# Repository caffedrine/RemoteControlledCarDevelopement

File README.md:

## RC Car Developement

Designing and implementing a remote controlled rover from zero to hero!

## Summary:
  1. Project information: [RC_Car_WordDoc.odt](docs/RC_Car_Developement.odt)
  2. Required list of components: [here](Components.md)
  3. How to build: [here](How-to-build.md)
  4. Firmware upload and debugging: [here](Firmware-upload.md)
  
*Costs:* ~60EUR

## Results

## Connections 

#### 1. Connection indicator LED
This is a LED whose meant is to indicate whether there is a connection established with car or not.
It have three states:
  1. Turned off - this mean that a connection is established with car and no further incoming connections will be accepted;
  2. Blinking - No clients connected to car AP nor Sockets are oppened;
  3. Blinking faster - Clients connected to AP but no sockets oppened. If use Java developed app, possibly application is not running.

#### 2. Traffic indicator LED
This is a LED whose meant is to act like any regular ethernet traffic indicator. Whether there is a data exchange between client and car this led will blink. Efficient feedback to confirm if your data is being received by car and vice-versa.

#### 3. Left QRE1113 IR Sensor
Connector for left wheel sensor.

#### 4. RESET Button
This is a push button which will reset car. Whether connection is not responding or you're unable to connect, presh this button and program will reset.

#### 5. Motors connector
Connect motors to this socket using the given pairs. First two entries for left motor and last two entries for right motor. In case motors are reversed, just switch polarity to get the correct rotation direction. 
PS: Do not cross connections between motors!!!

#### 6. IO0
This is a push button and is used to turn microcontroller into programming mode. Whether you want to upload a new firmware, you'll have to use this button in the following way:
Push IO0 and keep it pushed >> once RESET button (don't keep it pushed) >> release IO button. Now the microcontrolled will enter on programing mode and a new firmware can be uploaded using ping pins from point 7.

#### 7. Programming connectors
This is the socket used to upload a new firmware on mictrocontroller. Pins are active only when microcontroller is turned on on programming mode using point 6 (above).
Usually you coonnect pins to a Serial-2-USB converter.
**WARNING:** Logical levels are 0-3.3V. Applying 5V may broke the board.

#### 8. Right QRE1113 IR Sensor
Connector for right wheel sensor.

**Notes:**
  * future versions have a power switch on right-bottom edge;
  * micro USB connection is in bottom layer right beside motors connector;

## How to control the car
Turn the power on by connecting cable to powerbank and swith on. After few seconds, connection led should blink indicating that car is waiting for a incomming conenction. To control the car, two connection phases are required:
1. Connecting to AP - This is the exactly like connecting to any regular router or hotspot. This is possible because car will automatically will create an Access Point (hotspot) when is powered on. Just connect to that network!
In order to do this, you will need **AP Name** and **password**. Check here for credentials: [firmware](Arduino/)
Windows instructions: https://support.microsoft.com/en-us/help/17137/windows-setting-up-wireless-network

2. After you are connected, the connection led will blink a little bit faster. Now, now we need to make sure we are connected to right network. 
The following tool is required: [putty](http://www.putty.org/) - download and install PuTTy.
Launch and fill IP address with **192.168.4.1** and port **1337** and select "Telnet" for protocol, as in the following picture:

Then click open button (bottom).

At this point communication channel should be established with car. If everything is fine, the connection led should not blink anymore and you will get the following window:

We can use this terminal to send commands to car:
For example, type **>>>[G;20;3000]** and hit *Enter*. At this point, car will give feed back when command is received and executed:

Details about commands here: [Java Commands](Java/)

At this point, you can made your own application with joysticks and stuff and use TCP sockets to send commands! Check my other repositories as I already made some C++ and Qt Wrappers for TCP Sockets. Check Java folder as WiFi.java may be public :)

**Note:** You can also use mobile phone but use an application such as *Mobile Telnet* instead of PuTTy.

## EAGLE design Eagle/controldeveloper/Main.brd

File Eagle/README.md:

# Eagle files for PCB!

# Pinmap: 

# Schematic

# Final PCB

# Physical PCB

# Physical Board

## Tip:
  1. You can add an heat sink in case LM317 Voltage Regulator is getting hot.

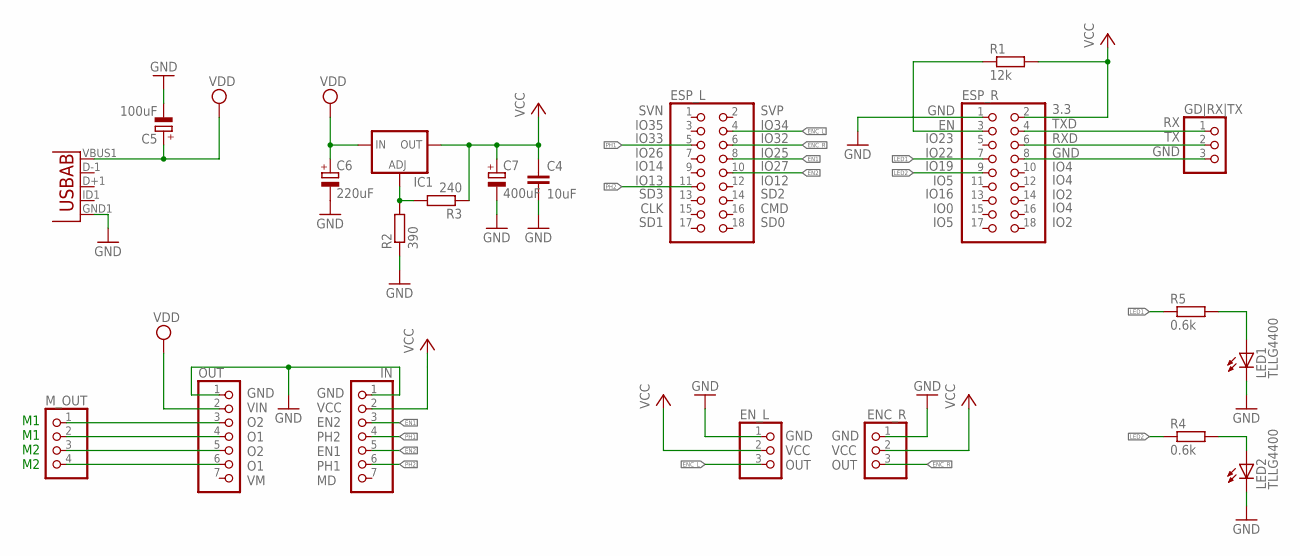
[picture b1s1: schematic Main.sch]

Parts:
C4: 10uF; C050-025X075
C5: 100uF; E2,5-6
C6: 220uF; E2,5-6
C7: 400uF; E2,5-6
ENC_R: PINHD-1X3; 1X03
EN_L: PINHD-1X3; 1X03
ESP_L: PINHD-2X9; 2X09
ESP_R: PINHD-2X9; 2X09
GD|RX|TX: PINHD-1X3; 1X03
IC1: LM317TS; 317TS
IN: PINHD-1X7; 1X07
LED1, LED2: TLLG4400; LED3MM
M_OUT: PINHD-1X4; 1X04
OUT: PINHD-1X7; 1X07
R1: 12k; 0207/10
R2: 390; 0207/10
R3: 240; 0207/10
R4, R5: 0.6k; 0207/10
U3: USB""; USB-MICRO-SMD

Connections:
EN1: ESP_L.8, IN.3
EN2: ESP_L.10, IN.5
ENC_L: EN_L.3, ESP_L.4
ENC_R: ENC_R.3, ESP_L.6
GND: C4.2, C5.-, C6.-, C7.-, ENC_R.1, EN_L.1, ESP_R.1, IN.1, LED1.K (C), LED2.K (C), OUT.1, R2.1, U3.GND1 (GND)
LED1: ESP_R.7, R5.1
LED2: ESP_R.9, R4.1
unnamed: M_OUT.1, OUT.3
unnamed: M_OUT.2, OUT.4
unnamed: M_OUT.3, OUT.5
unnamed: M_OUT.4, OUT.6
unnamed: ESP_R.4, GD|RX|TX.1
unnamed: ESP_R.6, GD|RX|TX.2
unnamed: IC1.1 (ADJ), R2.2, R3.2
unnamed: ESP_R.8, GD|RX|TX.3
unnamed: LED2.A, R4.2
unnamed: ESP_R.3, R1.1
unnamed: LED1.A, R5.2
PH1: ESP_L.5, IN.4
PH2: ESP_L.11, IN.6
VCC: C4.1, C7.+, ENC_R.2, EN_L.2, ESP_R.2, IC1.2 (OUT), IN.2, R1.2, R3.1
VDD: C5.+, C6.+, IC1.3 (IN), OUT.2, U3.VBUS1 (VBUS)

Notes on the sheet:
GND VCC EN2 PH2 EN1 PH1 MD
GND VIN O2 O1 O2 O1 VM
M1 M1 M2 M2
RX TX GND
GND VCC OUT
3.3 TXD RXD GND
IO4 IO2
GND EN
IO23 IO22
IO19 IO5
IO16 IO0
IO5
IO4
SVN IO35
IO33 IO26
IO14 IO13
SD3 CLK
SD1
SVP IO34
IO32 IO25
IO27 IO12
SD2 CMD
SD0

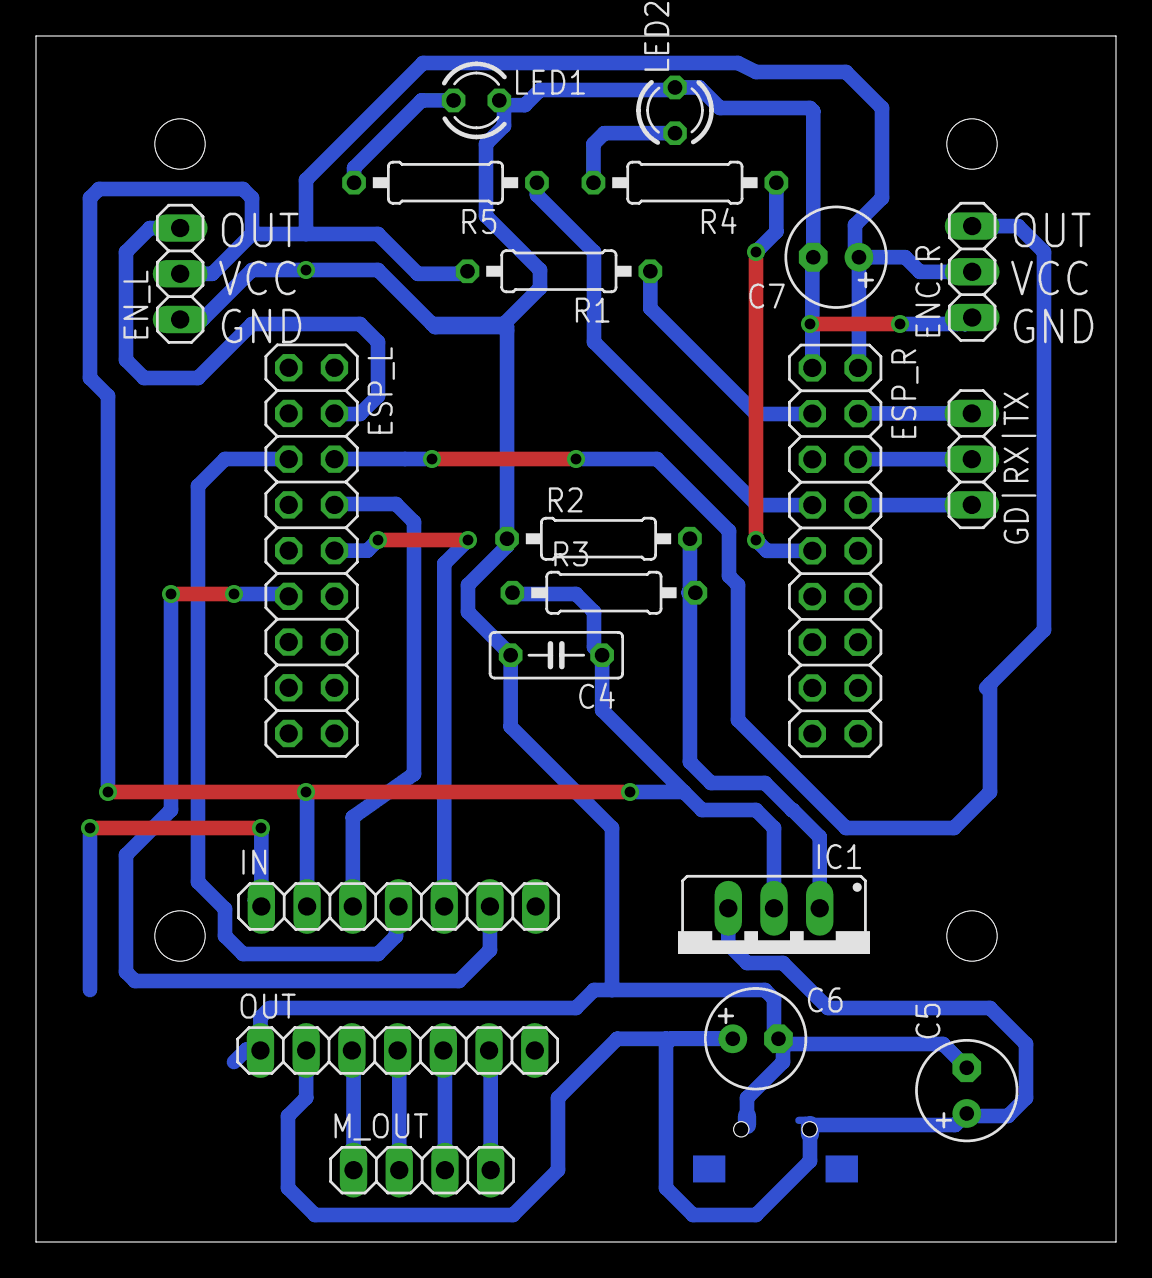
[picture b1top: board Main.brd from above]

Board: 2 copper layers, 60.0 x 67.0 mm, 21 parts (1 on the bottom side), 22 nets.

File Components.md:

# List of components
Before proceeding, make sure you have the possibility to print the frame of car using a 3D Printer! It is in folder 3D_Design. Also don't forget to print the wheels!
Also make sure you have the possibility to create Printed Circuit Boards (PCB).

### Main components required:
  1. **2x QRE1113** - SparkFun RedBot Sensor - Line Follower
     https://eckstein-shop.de/SparkFun-RedBot-Sensor-Line-Follower-EN
  2. **2x DC Motors + GearBox** - Recommended gear ratio: 120:1
     http://www.exp-tech.de/dagu-dc-gear-motor-paar-90-degree-sha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
  3. **1x DRV8835 Dual Motor Driver** - In case you don't want to make your own H bridges.
     http://www.exp-tech.de/drv8835-dual-motor-driver-carrier 
  4. **1x Espressif ESP-WROOM-32** - This is the WiFi 2.4 GHz module used to control car.
     https://eckstein-shop.de/Espressif-ESP-WROOM-32-EN
  5. **1x Wifi Module Adapter** - This will make life easier
     https://eckstein-shop.de/Adapter-Breakout-Board-for-ESP-32S-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
  6. **1x Plastic Wheel Ball**
     http://www.exp-tech.de/pololu-ball-caster-with-1-2-plastic-b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
  7. **1x Powerbank** - You can also find this on Amazon at better prices.
     https://www.tln-werbemittel.de/powerbanks/powerbank-akku-tow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
  8. **2xRubber O-Rings** - In order to get some aderency on wheels.
     https://www.hug-technik.com/shop/product_info.php?info=p2032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
  9. **1xUSB Micro B Connector**
     http://uk.farnell.com/amphenol-fci/10104110-0001lf/micro-usb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
  10. **Power ON/OFF switch**
      https://eckstein-shop.de/Adafruit-Breadboard-friendly-SPDT-S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
  11. **6.5mm Screws**
  	  https://www.conrad.biz/de/blechschrauben-22-mm-65-mm-kreuzsc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
     
### Electrical components:
  1. 1x LM317 Voltage regulator
  2. 2x Reasonable leds
  3. 10x Pinheaders Male
  4. 25x Pinheader Female
  5. 2x 20 Double Pinheader Female
  6. 2x Reasonable leds
  7. 2x 0.6~0.9K Resistors
  8. 1x 12k Resistors
  9. *1x 390 Ohm Resistor*
  10. *1x240 Ohm Resistor*
  11. Electrolithic capacitors: 1x100uF, 2x220uF or lower.
  12. Ceramic capacitors: 1x10uF  

### Components/Tools required to build prototype
  1. **1x FTDI1232** - This is an adapter which allows you to write program to WiFi Module. You can make your own it's not hard but be aware that you need to convert logical levels from USB from [0-5V] to [0-3.3V]
     https://www.amazon.de/AZDelivery-Adapter-FT232RL-Serial-Ardu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
  2. **Optional:** If you want to test and debug code easily, you may want to pick up an Sparkfun ESP32 Thing - Developement board. Build code on that board and upload to ESP32-WROOM when it is finished.
     http://www.exp-tech.de/en/sparkfun-esp32-thing?___from_store=de

#### Other components
Screws, wires, zipties and stuff like this :)
	 
**PS: If the links expired, let those guys know: http://web.archive.org **

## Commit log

2017-06-20 Eagle design changed.
2017-06-22 .gitign support for windows
2017-06-22 Eagle gitignore updates
2017-06-22 Gitign
2017-06-22 Updated eagle files
2017-06-27 Added code for ESP32Wroon
2017-06-27 Added an readme
2017-06-27 Working on wroom code!
2017-06-27 Added encoders on Eagle Project
2017-06-27 Working WROOM COde
2017-06-28 Pinmap for WROOM updated
2017-06-28 Eagle proj - redesigned
2017-06-28 3D Design is just perfect now ^_^
2017-06-28 Eagle SCH Looks more profi ^_^
2017-06-28 Finished eagle board!
2017-06-28 Added PCB Pinmap and Readme
2017-06-28 Java gitignore
2017-06-29 Added schematic picture
2017-06-29 Board picture
2017-06-29 Final version of Eagle board
2017-06-29 Updated 3D Design
    Larger holes to fix motors.
2017-06-29 IR Sensors calibrated with wheels
2017-07-01 lala
2017-07-01 Organized directories
2017-07-02 PID
    Pid works pretty good at power 80.
2017-07-02 Motors Driver Lib - Changed
2017-07-03 More stable version of PID
    Works perfect in interval [45-75]
2017-07-05 Bugs in Eagle Design were corrected!
2017-07-05 Organized directories and updated some images
2017-07-05 Working version of PID with computeSteps(nr) function.
    Known bug: Compute steps function workd only forward. On different
    directions there is a conflicat between updateSlaveMotor() and
    computeSteps(...)
2017-07-05 All functions works perfectly!
    Patched bug in computeSteps(...) now function works like a charm and
    uses pid function to make rotation more linear.
2017-07-05 Added some usefull comments!
2017-07-06 Updated list of components
2017-07-06 Updated components list
2017-07-06 Updated Eagle README
2017-07-06 **** **First RELEASE** ****
    Fully working version of code and Eagle design!
2017-07-06 ****Release*** NO MORE Radio bugs
2017-07-07 No more bugs on schematic
    The left motors starts no more before init() sequence.
2017-07-07 ***WORKING VERSION***
2017-07-07 Arduino password and ap name added on readme
2017-07-07 Updated main readme.
2017-07-07 Main readme updated
2017-07-11 Added switch to components list
2017-07-11 Eagle PCB Redesigned
    * Routes were optimized
    * Space for heat sink added
    * Added Power ON/OFF switch
2017-07-11 Updated readmes
2017-07-20 Added screws on components list
2017-08-01 Almost done Java app
2017-08-03 Added documentation
2017-08-03 Added java source code unde password zip
2017-08-03 Added java code main changes list
2017-08-04 Added docs
2017-08-04 Update Java archive
2017-08-04 Updated Java girignore
2017-08-15 changed main readme
2017-08-16 Reviewed docs
2017-08-24 optimizations
2017-08-24 last test
